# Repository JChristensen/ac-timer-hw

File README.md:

# AC timer  
https://github.com/JChristensen/ac-timer-hw  
README file  
Jack Christensen  
Jul-2023

## License
  
This work is licensed under the [Creative Commons Attribution-ShareAlike 4.0 International License](https://creativecommons.org/licenses/by-sa/4.0/).

## See also
[https://github.com/JChristensen/dehumid](https://github.com/JChristensen/dehumid) (firmware)  
[https://github.com/JChristensen/ac-timer-panel](https://github.com/JChristensen/ac-timer-panel)

## Construction
The project is assembled in a square metallic electrical box, 4 in. x 2⅛ in. deep (30.3 cu. in.), with ½ in. knockouts. The box acts as a heat sink for the solid state relay; use heat sink grease when fastening the SSR to the box.

See the links above for firmware and for a small PCB to facilitate mounting the LEDs and pushbutton switch.

See the bill of materials [in this repo](https://github.com/JChristensen/ac-timer-hw/blob/master/bom.csv) and at [Mouser Electronics](https://www.mouser.com/ProjectManager/ProjectDetail.aspx?AccessID=c48290707f).

## Sample assembly

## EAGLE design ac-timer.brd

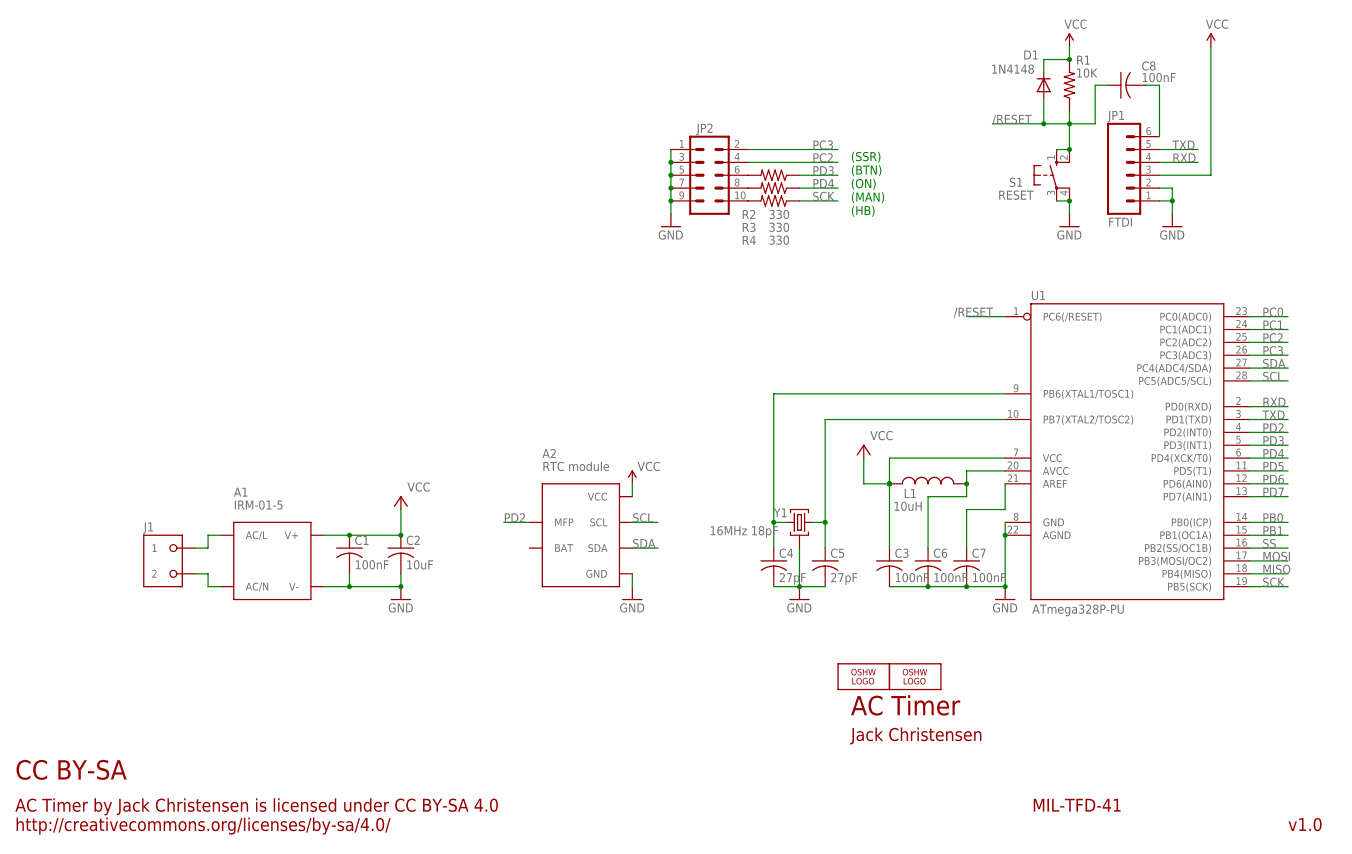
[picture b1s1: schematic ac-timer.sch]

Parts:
A1: IRM-01-5; IRM-01
A2: RTC module; RTC79412
C1, C3, C6, C7, C8: 100nF; M0805
C2: 10uF; M0805
C4, C5: 27pF; M0805
D1: 1N4148; SOD-323F
J1: OST-TB-20.20IN; OST-TB-2-0.20
JP1: FTDI; 1X06_LOCK
JP2: M05X2PTH; AVR_ICSP
L1: 10uH; M0805
LOGO1, LOGO2: OSHW_LOGO_8MILX0100-NT; OSHW_8X100_NOTEXT
R1: 10K; M0805
R2, R3, R4: 330; M0805
S1: RESET; B3F-10XXOCT
U1: ATmega328P-PU; DIL28-3
Y1: 16MHz 18pF; RESONATOR

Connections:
/RESET: C8.1, D1.A, R1.1, S1.1 (S), S1.2 (S1), U1.1 (PC6(/RESET))
GND: A1.V-, A2.8 (GND), C1.2, C2.2, C3.2, C4.2, C5.2, C6.2, C7.2, JP1.1, JP1.2, JP2.1, JP2.3, JP2.5, JP2.7, JP2.9, S1.3, S1.4 (P1), U1.8 (GND), U1.22 (AGND), Y1.2
MISO: U1.18 (PB4(MISO))
MOSI: U1.17 (PB3(MOSI/OC2))
unnamed: JP2.10, R4.2
unnamed: JP2.8, R3.2
unnamed: JP2.6, R2.2
unnamed: C5.1, U1.10 (PB7(XTAL2/TOSC2)), Y1.3
unnamed: C6.1, L1.2, U1.20 (AVCC)
unnamed: C4.1, U1.9 (PB6(XTAL1/TOSC1)), Y1.1
unnamed: C7.1, U1.21 (AREF)
unnamed: A1.AC/N, J1.P$2 (2)
unnamed: A1.AC/L, J1.P$1 (1)
PB0: U1.14 (PB0(ICP))
PB1: U1.15 (PB1(OC1A))
PC0: U1.23 (PC0(ADC0))
PC1: U1.24 (PC1(ADC1))
PC2: JP2.4, U1.25 (PC2(ADC2))
PC3: JP2.2, U1.26 (PC3(ADC3))
PD2: A2.3 (MFP), U1.4 (PD2(INT0))
PD3: R2.1, U1.5 (PD3(INT1))
PD4: R3.1, U1.6 (PD4(XCK/T0))
PD5: U1.11 (PD5(T1))
PD6: U1.12 (PD6(AIN0))
PD7: U1.13 (PD7(AIN1))
RST: C8.2, JP1.6
RXD: JP1.4, U1.2 (PD0(RXD))
SCK: R4.1, U1.19 (PB5(SCK))
SCL: A2.6 (SCL), U1.28 (PC5(ADC5/SCL))
SDA: A2.5 (SDA), U1.27 (PC4(ADC4/SDA))
SS: U1.16 (PB2(SS/OC1B))
TXD: JP1.5, U1.3 (PD1(TXD))
VCC: A1.V+, A2.7 (VCC), C1.1, C2.1, C3.1, D1.K, JP1.3, L1.1, R1.2, U1.7 (VCC)

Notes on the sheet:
AC Timer
Jack Christensen
AC Timer by Jack Christensen is licensed under CC BY-SA 4.0 http://creativecommons.org/licenses/by-sa/4.0/
CC BY-SA
v1.0
MIL-TFD-41
(SSR) (BTN) (ON) (MAN) (HB)

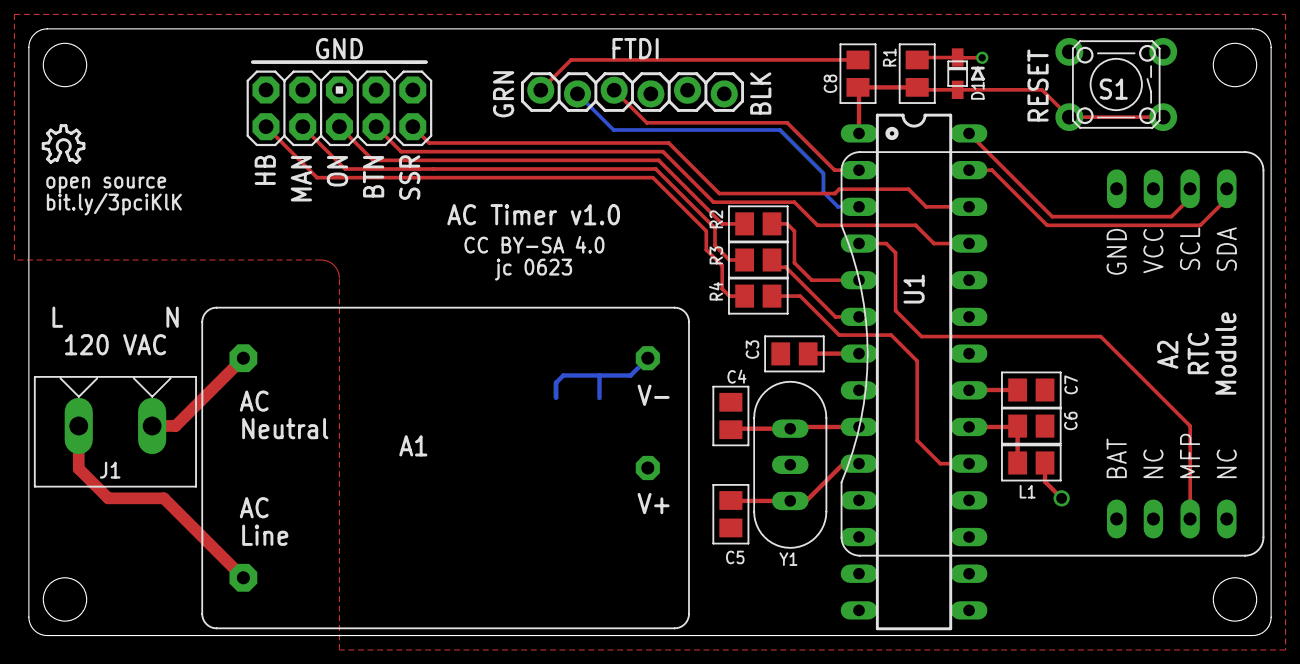
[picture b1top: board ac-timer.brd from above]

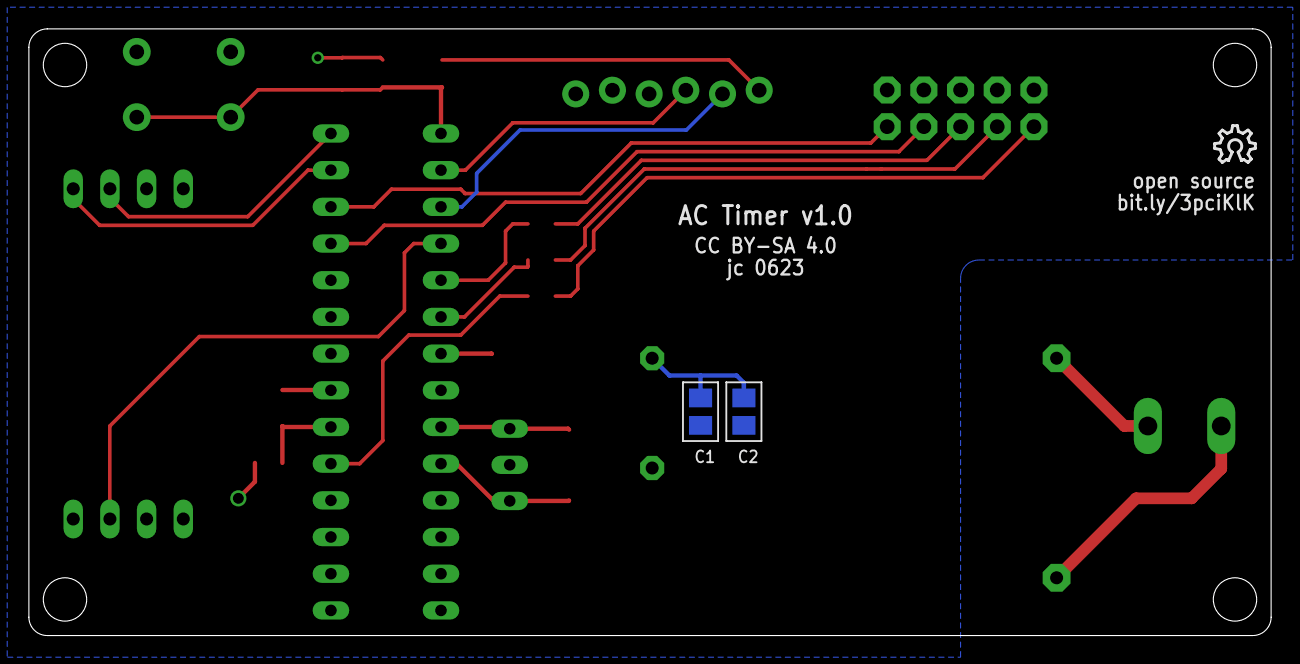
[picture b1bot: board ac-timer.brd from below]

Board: 2 copper layers, 86.0 x 42.0 mm, 24 parts (3 on the bottom side), 23 nets.

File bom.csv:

AC Daily Timer,,,,,
Copyright (C) 2023-2024 by Jack Christensen and licensed under CC-BY-SA-4.0.,,,,,
https://www.mouser.com/ProjectManager/ProjectDetail.aspx?Acc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,,,,,
,,,,,
Part #,Qty,Mouser #,Description,Manufacturer,Mfr. #
A1,1,709-IRM01-5,AC/DC Power Module 1W 5V 200mA,MEAN WELL,IRM-01-5
A2,1,n/a,Real-time clock module,JChristensen,https://github.com/JChristensen/rtc79412
"C1,3,6,7,8",5,581-08053C104KAT4A,MLCC 25V 0.1uF 0805,KYOCERA AVX,08053C104KAT4A
C2,1,187-CL21A106KPCLQNC,MLCC 10uF 10V 0805,Samsung Electro-Mechanics,CL21A106KPCLQNC
"C4,5",2,77-VJ0805A270GXXPBC,MLCC 0805 27pF 25volts C0G 2%,Vishay,VJ0805A270GXXPW1BC
D1,1,512-1N4148WS,Small Signal Diode,onsemi,1N4148WS
J1,1,651-1935161,"Terminal block, 2 position, 5.08mm pitch",Phoenix Contact,1935161
JP1,1,,"2.54mm header, male, 1x6",generic,
JP2,1,,"2.54mm header, male, 2x5",generic,
L1,1,963-LBR2012T100K,Inductor 0805 10uH,TAIYO YUDEN,LBR2012T100K
R1,1,660-RK73H1JTTDD1002F,Thick Film Resistor 10k ohms,KOA Speer,RK73H1JTTDD1002F
"R2,3,4",3,660-RK73H1JTTDD3300F,Thick Film Resistor 330 ohms,KOA Speer,RK73H1JTTDD3300F
S1,1,653-B3F-1020,Tactile Button Switch,Omron,B3F-1020
U1,1,556-ATMEGA328P-PU,8-bit Microcontroller,Microchip,ATMEGA328P-PU
Y1,1,774-ATS16B-E,"Crystal, 16MHz 18pF 30ppm",CTS,ATS16B-E
,1,,"Solid State Relay, 40A",SparkFun Electronics,COM-13015
,1,,"Square metallic electrical box, 4 in. x 2⅛ in. deep (30.3 cu. in.), ½ in. knockouts",,
,1,,Cover for above box,,
,1,,Duplex receptacle,,
,1,,14-gauge power cable,,
,1,,½ in. cable clamp,,
,1,,"Red LED, 5mm",generic,
,1,,"Yellow LED, 5mm",generic,
,1,,"Green LED, 5mm",generic,
,1,,Pushbutton switch,generic,"SparkFun COM-11992, Jameco 26623, or similar"

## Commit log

2023-06-23 Initial commit.
2023-06-23 Rotate AC input terminal block.
2023-06-24 Production candidate 01
2023-06-24 Small routing and silk tweaks.
2023-06-25 Widen AC traces.
2024-05-31 Add README, LICENSE, BOM, gerbers.zip

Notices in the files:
parts and their libraries:
SparkFun: Licensing: CC v3.0 Share-Alike You are welcome to use this library for commercial purposes.
